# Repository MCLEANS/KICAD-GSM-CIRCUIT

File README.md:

# KICAD-GSM-CIRCUIT
A sample GSM circuit for KiCAD

## Branch to manage the circuit board routing

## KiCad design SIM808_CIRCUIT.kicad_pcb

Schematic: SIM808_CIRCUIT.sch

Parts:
C1: 10pF; CP_Elec_5x4.4
C2: 10uF; CP_Elec_5x4.4
C3: 100uF; C_0805_2012Metric
C4: 33pF; C_0805_2012Metric
C5: 10pF; C_0805_2012Metric
C6, C7: 22pF; C_0805_2012Metric
D1, D2, D3, D4: LED; LED_0603
D5: DIODE; D_0805_2012Metric
D6: SMF05C; SC70-6
H1, H2, H3, H4: MountingHole; MountingHole_3.5mm
J1: USB_B_Micro; USB_Micro-B_Molex-105017-0001
J2: SMA-J-P-H-RA-TH1; SAMTEC_SMA-J-P-H-RA-TH1
J3: 693012040811; WURTH_693012040811
J4: AVR-ISP-6; IDC-Header_2x03_P2.54mm_Vertical
J5: U.FL-R-SMT(01); HRS_U.FL-R-SMT(01)
R1: 10K; R_0805_2012Metric
R2, R4, R5: 220ohm; R_0805_2012Metric
R3: 1K; R_0805_2012Metric
SW1, SW2: SW_Push; SW_PUSH_6mm_H5mm
U1: MCP73811T-420I-OT; SOT-23-5
U2: SIM808; XCVR_SIM808
U3: 74ABT125D; SOIC127P600X175-14N
U4: ATmega328-AU; TQFP-32_7x7mm_P0.8mm
Y1: Crystal; Crystal_HC49-U_Vertical

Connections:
1.8V: D6.1 (C1), J3.C1, U2.29 (SIM_VDD)
2.8V: R1.1, U2.7 (VDD_EXT)
+5V: C2.1, D1.2 (A), J1.1 (VBUS), J4.2 (VCC), U1.4 (VDD), U3.14 (VCC), U4.4 (VCC), U4.6 (VCC), U4.18 (AVCC)
AVR_RST: J4.5 (~RST), SW2.1, U4.29 (~RESET~/PC6)
GND: C1.2, C2.2, C3.2, C4.2, C5.2, C6.2, C7.2, D2.1 (K), D5.1 (K), D6.2 (A), J1.5 (GND), J1.6 (Shield), J2.2, J2.3, J2.4, J2.5, J3.C5, J4.6 (GND), J5.1, J5.2, R4.1, R5.1, SW1.2, SW2.2, U1.1 (CEN), U1.2 (VSS), U2.1 (GND), U2.2 (GND), U2.3 (GND), U2.18 (GND), U2.28 (GND), U2.34 (GND), U2.36 (GND), U2.40 (GND), U2.51 (GND), U2.52 (GND), U2.54 (GND), U2.64 (GND), U2.65 (GND), U2.67 (GND), U2.68 (GND), U3.1 (1~OE), U3.4 (2~OE), U3.7 (GND), U3.10 (3~OE), U3.13 (4~OE), U4.3 (GND), U4.5 (GND), U4.21 (GND)
GSMRST: U2.16 (~RESET~)
MISO: J4.1 (MISO), U4.16 (PB4)
MOSI: J4.4 (MOSI), U4.15 (PB3)
NETSTAT: U2.50 (NETLIGHT), U3.9 (3A)
NETSTAT_5V: D3.2 (A), U3.8 (3Y)
unnamed: C6.1, U4.8 (XTAL2/PB7), Y1.2
unnamed: C7.1, U4.7 (XTAL1/PB6), Y1.1
unnamed: D1.1 (K), R2.2
unnamed: D2.2 (A), R3.2
unnamed: D3.1 (K), R5.2
unnamed: D4.1 (K), R4.2
unnamed: J2.1, U2.66 (GSM_ANT)
unnamed: J5.3, U2.35 (GPS_ANT)
unnamed: R2.1, R3.1, U1.5 (PROG)
POWERSTAT: U2.49 (STATUS), U3.12 (4A)
PWRKEY: SW1.1, U2.8 (PWRKEY)
PWRSTAT_5V: D4.2 (A), U3.11 (4Y)
RING: U2.10 (RI), U3.5 (2A)
RING_5V: U3.6 (2Y)
RTS: R1.2, U2.13 (RTS)
SCK: J4.3 (SCK), U4.17 (PB5)
SIM_CLK: D6.4 (C3), J3.C3, U2.31 (SIM_CLK)
SIM_DATA: D6.3 (C2), J3.C7, U2.30 (SIM_DATA)
SIM_RST: D6.5 (C4), J3.C2, U2.32 (SIM_RST)
SIM_RXD: U2.15 (RXD), U4.31 (PD1)
SIM_TXD: U2.14 (TXD), U3.2 (1A)
UART_TX: U3.3 (1Y), U4.30 (PD0)
VBAT: C3.1, C4.1, C5.1, D5.2 (A), U1.3 (VBAT), U2.4 (VBAT), U2.5 (VBAT), U2.6 (VBAT)
VRTC: C1.1, U2.17 (VRTC)

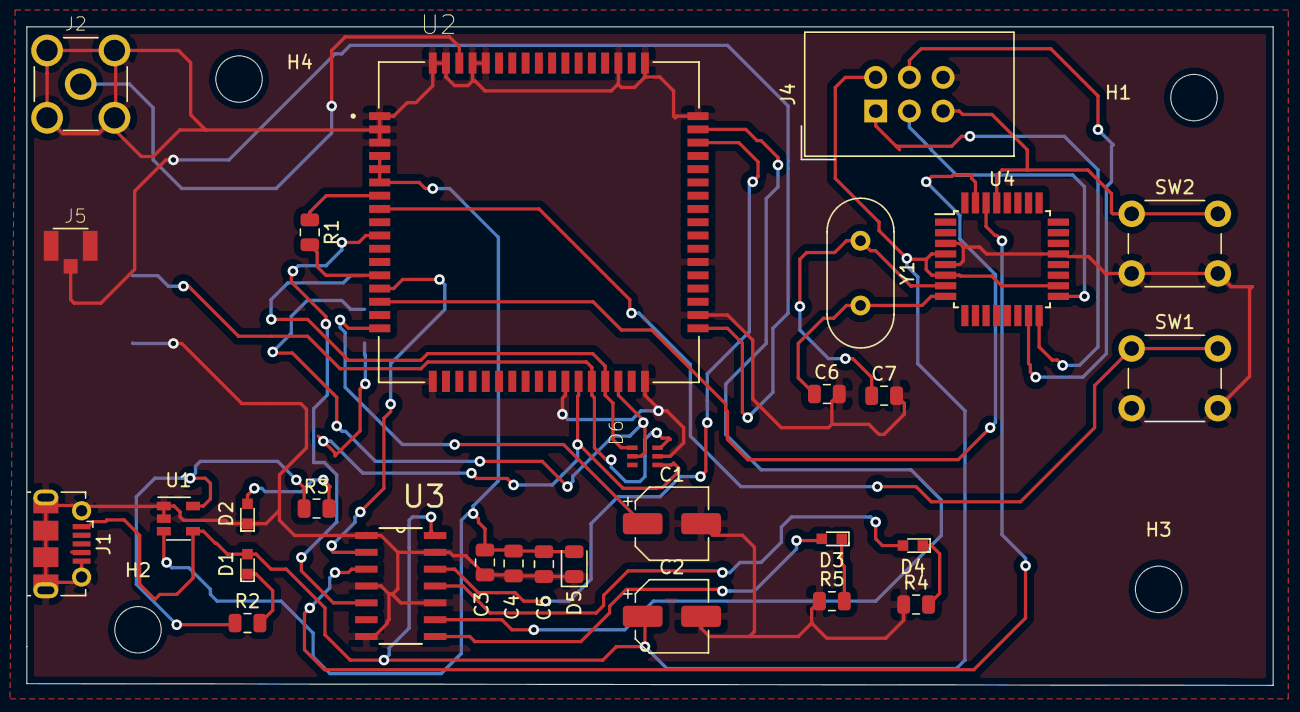
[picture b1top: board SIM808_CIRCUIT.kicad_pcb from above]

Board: 2 copper layers, 94.0 x 49.7 mm, 34 parts (1 on the bottom side), 32 nets.

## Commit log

2020-03-17 Schematic file
2020-03-17 project file for kicad'
2020-03-17 project netlist
2020-03-17 unrouted layout
2020-03-17 connected ISP line to AVR
2020-03-17 updated netlist
2020-03-17 Half routed
2020-03-17 kiCAD project files
2020-03-18 routed GSM UART lines
2020-03-18 routed VRTC and RING line
2020-03-18 Final routing attempt
2020-03-18 completed routing
2020-03-18 GSM antennae moved to new position
2020-03-18 routed circuit board
2020-03-19 documentation
2020-03-26 circuit board schematic
2020-03-26 circuit components netlist
2020-03-26 circuit board layout
2020-03-26 v1 sample
